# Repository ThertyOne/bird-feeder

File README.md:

# 🐦 Solar Bird Feeder

## 📘 Opis projektu
Projekt to **autonomiczny karmnik dla ptaków z funkcją wykonywania zdjęć**, oparty na module **ESP32-CAM**, zasilany z akumulatora **Li-Po 3,7 V / 2200 mAh**, ładowanego przez ładowarkę **TP4056** z panelem solarnym **6 V / 1 W** (możliwość połączenia 2 paneli szeregowo).  

Z wyjścia baterii energia trafia do **przetwornicy boost 5 V**, zbudowanej od podstaw na bazie generatora **PWM LMC555** i MOSFETa **IRLML6344**, która zasila ESP32 i peryferia – **serwo sterujące karmnikiem, LEDy oświetleniowe oraz czujniki**. Masa wszystkich modułów jest wspólna.  

Ładowanie z panelu odbywa się przez **diodę SS34** i **polyfuse 500 mA**, a napięcie akumulatora jest monitorowane przez dzielnik rezystorowy podłączony do ADC ESP.  

Po wykryciu ruchu przez czujnik ESP wychodzi z trybu **deep sleep**, włącza LED, wykonuje zdjęcie i wysyła je przez Wi-Fi na serwer, po czym ponownie przechodzi w uśpienie, oszczędzając energię. **Peryferia** (serwo, LEDy) są zasilane poprzez **klucz MOSFET**, który odcina zasilanie, gdy peryferia nie działają.

---

## ⚙️ Główne założenia
- Zasilanie autonomiczne: **panel solarny + akumulator Li-Po 3.7 V / 2200 mAh**
- Mikrokontroler i kamera: **ESP32-CAM (OV2640)**
- Komunikacja: **Wi-Fi**, opcjonalnie **LoRaWAN** w przyszłości
- Peryferia:
  - **Ultradźwiękowy czujnik / PIR** – detekcja obecności ptaka
  - **Serwo** – mechanizm podawania karmy
  - **Blue LED matrix 4x4** – doświetlenie sceny podczas zdjęcia
- ESP32 w trybie **deep sleep**, wybudzanie po przerwaniu z czujnika
- Przesyłanie zdjęcia i metadanych (data, godzina) do serwera lub lokalnej bazy danych

---

## ⚡ Przetwornica boost 5 V
- Źródło PWM: **LMC555 @ ~100 kHz, 3.3 V**
- MOSFET: **IRLML2502 / IRLML6344**
- Cewka: **15 μH**
- Dioda: **SS34**
- Kondensator wyjściowy: **4700 μF**
- Ograniczenie napięcia: **Zener 5 V**
- Funkcja: podnosi napięcie z 3,7 V akumulatora Li-Po do stabilnych 5 V dla ESP32 i peryferiów

---

## 🔋 Szacowane zużycie prądu
| Moduł            | Tryb/obciążenie             | Prąd (mA) |
|-----------------|----------------------------|------------|
| ESP32-CAM       | Deep sleep                 | 0.1 – 0.2 |
| ESP32-CAM       | Aktywne (Wi-Fi + foto)     | 180 – 250 |
| Serwo           | Ruch                        | 150 – 200 |
| LEDy            | Max 4 LED                   | 80 – 100 |
| Czujniki        | Idle                        | 2 – 5      |

**Średni pobór prądu:** ~10–30 mA przy większości czasu w deep sleep.  
**Maksymalny chwilowy pobór:** ~500 mA przy jednoczesnym ruchu serwa i LED.

---

## 💡 Sposoby oszczędzania energii
- ESP32 w **deep sleep**, wybudzenie tylko przy wykryciu ruchu
- Peryferia (LED, serwo) zasilane przez **MOSFET**, odcięcie zasilania gdy nieaktywne
- Minimalizacja czasu pracy Wi-Fi i kamer
- Możliwość zmniejszenia jasności LED i liczby LED w pierścieniu
- Optymalizacja częstotliwości wybudzeń w zależności od natężenia odwiedzin ptaków

---

## ☀️ Energia z baterii i paneli
- **Akumulator Li-Po:** 3,7 V / 2200 mAh → **8,14 Wh**
- **Panel solarny:** 6 V / 1 W → maksymalny prąd ładowania ~167 mA (przy pełnym słońcu)
- **2 panele szeregowo:** napięcie 12 V / prąd ~83 mA, dalej prostownik i TP4056
- **Przetwornica boost 5 V:** sprawność ~85 % → prąd pobierany z akumulatora = Iout × 5 V / (η × 3,7 V)
- **Szacowany średni pobór prądu ESP32 + peryferia:** 50 mA @ 5 V  
  I_bat ≈ (5V * 0.05A) / (0.85 * 3.7V) ≈ 79,5 mA
- **Czas pracy na baterii bez słońca:**  
  Czas pracy na baterii ≈ 2200 mAh / 79,5 mA ≈ 27,7 h ≈ 1,15 dnia
- **Chwilowe piki prądu** (serwo + LED + Wi-Fi): ~500 mA @ 5 V → Ibat_peak ≈ 800 mA  
- **Przy słonecznej pogodzie** panele mogą praktycznie utrzymać akumulator w pełnym stanie, a nawet doładować go na zapas (np. 4–5 h słońca → ~4 Wh energii)

---

## 🔧 Uwagi do przetwornicy
- Układ **boost 5 V** przy chwilowych pikach prądu (serwo + LED + Wi-Fi) mogą wystąpić spadki napięcia
- Kondensator 4700 μF pomaga w wygładzaniu napięcia przy skokach prądowych
- Zener 5 V chroni ESP32 przed przepięciem, ale warto monitorować temperaturę MOSFETa i cewki przy pełnym obciążeniu
- Ewentualne zwiększenie cewki lub dodanie małego kondensatora ceramicznego przy MOSFET zwiększy stabilność przy dużym poborze

---

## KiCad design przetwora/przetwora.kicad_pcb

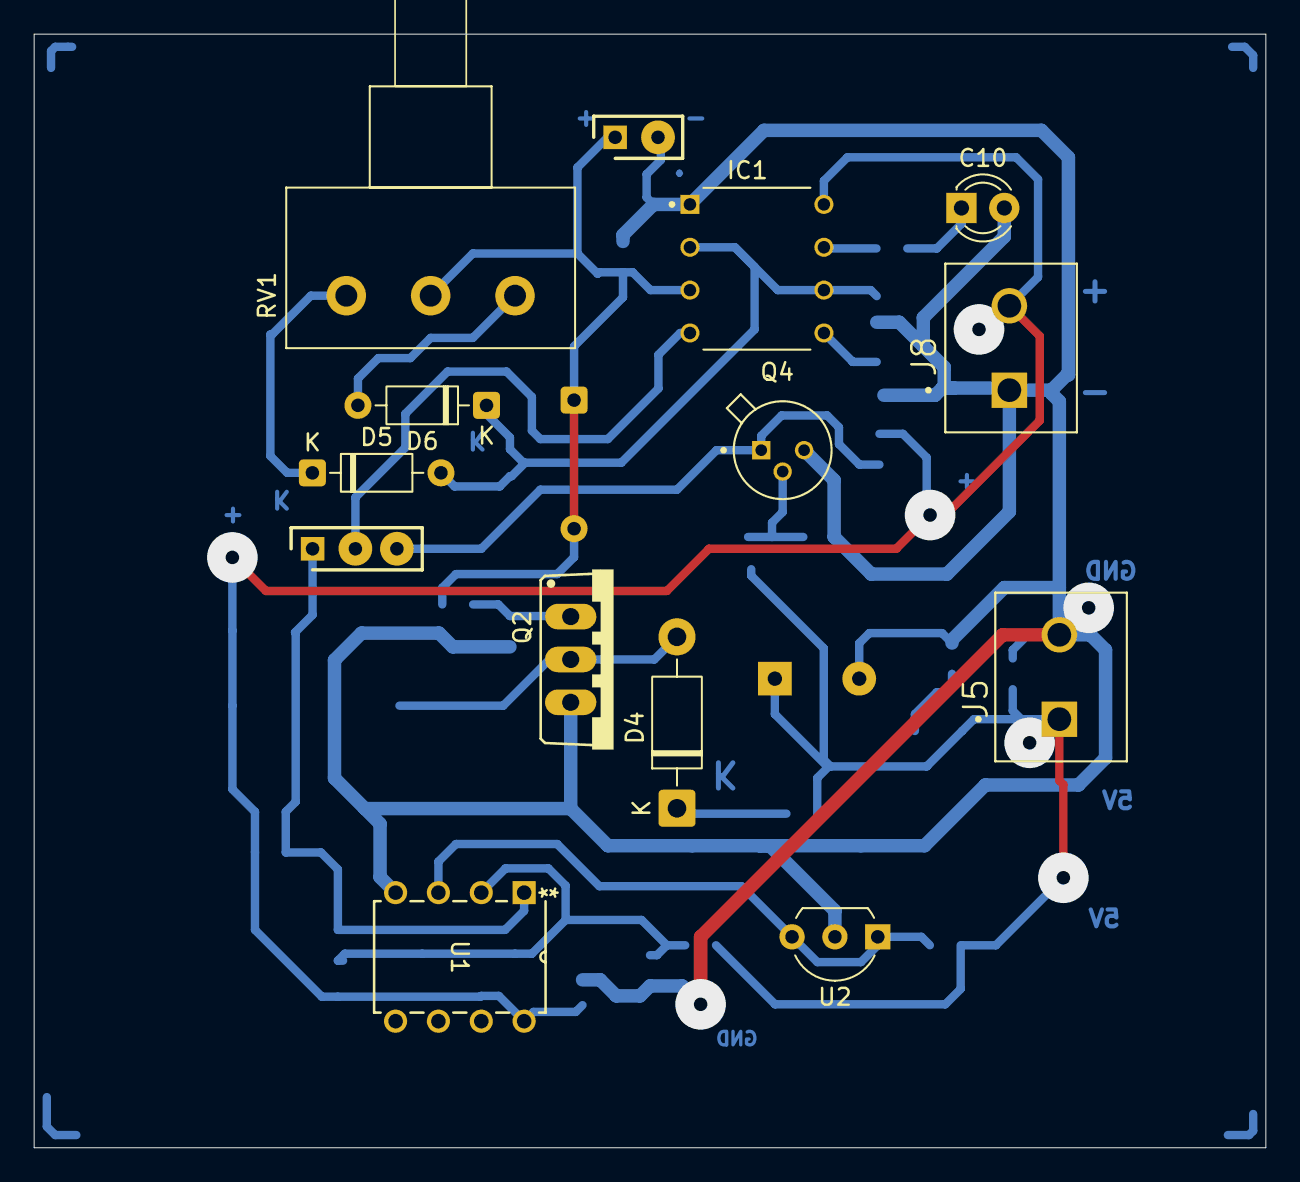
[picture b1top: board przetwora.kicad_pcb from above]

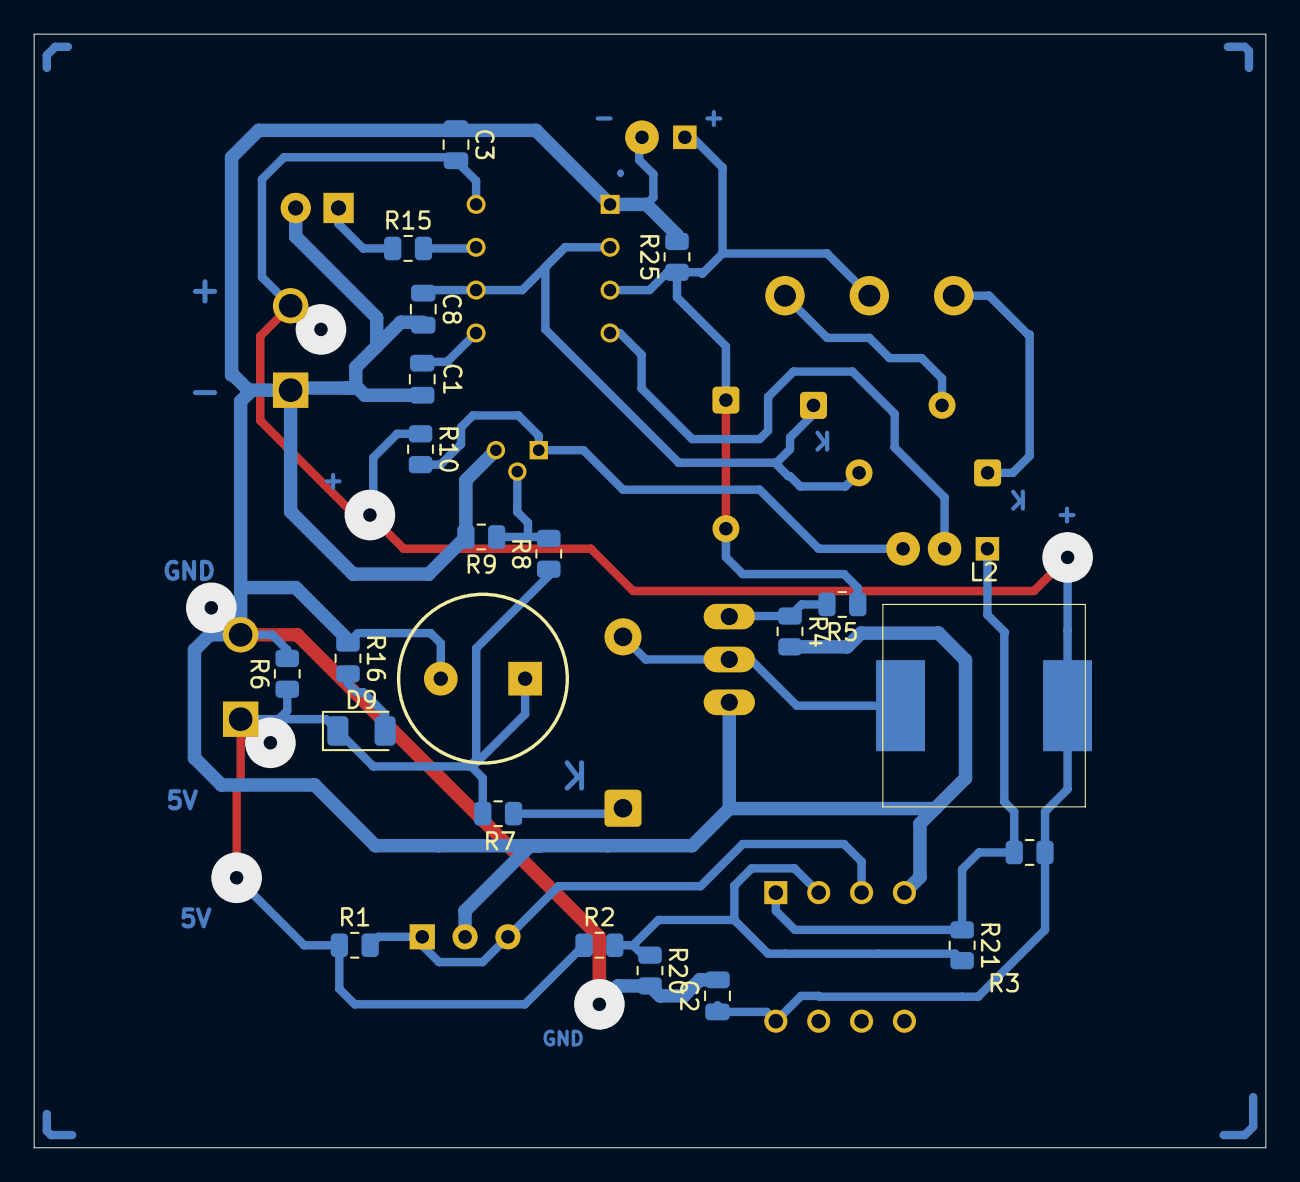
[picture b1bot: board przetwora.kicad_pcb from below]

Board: 2 copper layers, 73.0 x 66.0 mm, 37 parts (22 on the bottom side), 18 nets.

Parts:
C1, C8: 10n; C_0805_2012Metric
C2, C3: 100n; C_0805_2012Metric
C8#2: 4700 μ; electrolytic_CAPPRD500W65D1000H2700
C10: 100n; LED_D3.0mm
D4: 1N5818; D_DO-41_SOD81_P10.16mm_Horizontal
D5, D5#2, D6: 1N4148; D_DO-35_SOD27_P7.62mm_Horizontal
D9: 5.1 V; D_1206_3216Metric
IC1: lmc555; LMC555
J5: 5V_step_up; roaster_3_5
J6, J6#2: cont_3_5; pin_2_RHDR4W60P0X254_1X4_1016X250X840P_1
J8: baterry; roaster_3_5
L2: ETQP4M150KFN; cewka_DE1207
Q2: IRF740; irf740_TO220BV
Q4: NPN; 2N2222_TO127P580H530-3
R1: 680; R_0805_2012Metric
R2, R3, R4, R15, R20, R25: 10k; R_0805_2012Metric
R5, R10: 100; R_0805_2012Metric
R6: load test; R_0805_2012Metric
R7: 6.8; R_0805_2012Metric
R8: 4.7k; R_0805_2012Metric
R9: 1k; R_0805_2012Metric
R16: 470; R_0805_2012Metric
R21: 470k; R_0805_2012Metric
RV1: 10k; Potentiometer_Omeg_PC16BU_Horizontal
U1: LM393P; LM393
U2: TL431D; TO-92L_Inline_Wide

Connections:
+2V5: R1.2, U1.3 (1IN+), U2.1 (K), U2.3 (REF)
BAT: C2.1, C3.2, IC1.8 (V+), J8.2, L2.2, R3.1, R10.1, U1.8 (VCC)
GND: C1.2, C2.2, C3.1, C8.2, C10.2 (A), IC1.1 (GND), J5.2, J8.1, Q2.S, Q4.3 (E), R4.2, R6.2, R9.2, R16.1, R20.2, R25.2, U1.4 (GND), U2.2 (A)
unnamed: D4.1 (K), R7.1
unnamed: C10.1 (K), R15.1
unnamed: D4.2 (A), L2.1, Q2.D
unnamed: D5.1 (K), RV1.3
unnamed: D6.2 (A), RV1.1
unnamed: D9.2 (A), R16.2
unnamed: C1.1, IC1.5 (CV)
unnamed: IC1.7 (DIS), R15.2
unnamed: Q2.G, R4.1, R5.2
unnamed: Q4.2 (B), R8.2, R9.1
unnamed: R2.2, R20.1, R21.2, U1.2 (1IN-)
PWM_out: D5#2.1 (K), D5#2.2 (A), IC1.3 (OUT), R5.1, R25.1, RV1.2
reset: IC1.4 (~RST), J6.1, J6.2, J6.3 (2), Q4.1 (C), R3.2, R10.2, R21.1, U1.1 (1OUT)
step_up: D9.1 (K), J5.1, R1.1, R2.1, R6.1, R7.2, R8.1
trig: C8.1, D5.2 (A), D6.1 (K), IC1.2 (~TRIG), IC1.6 (THRS)

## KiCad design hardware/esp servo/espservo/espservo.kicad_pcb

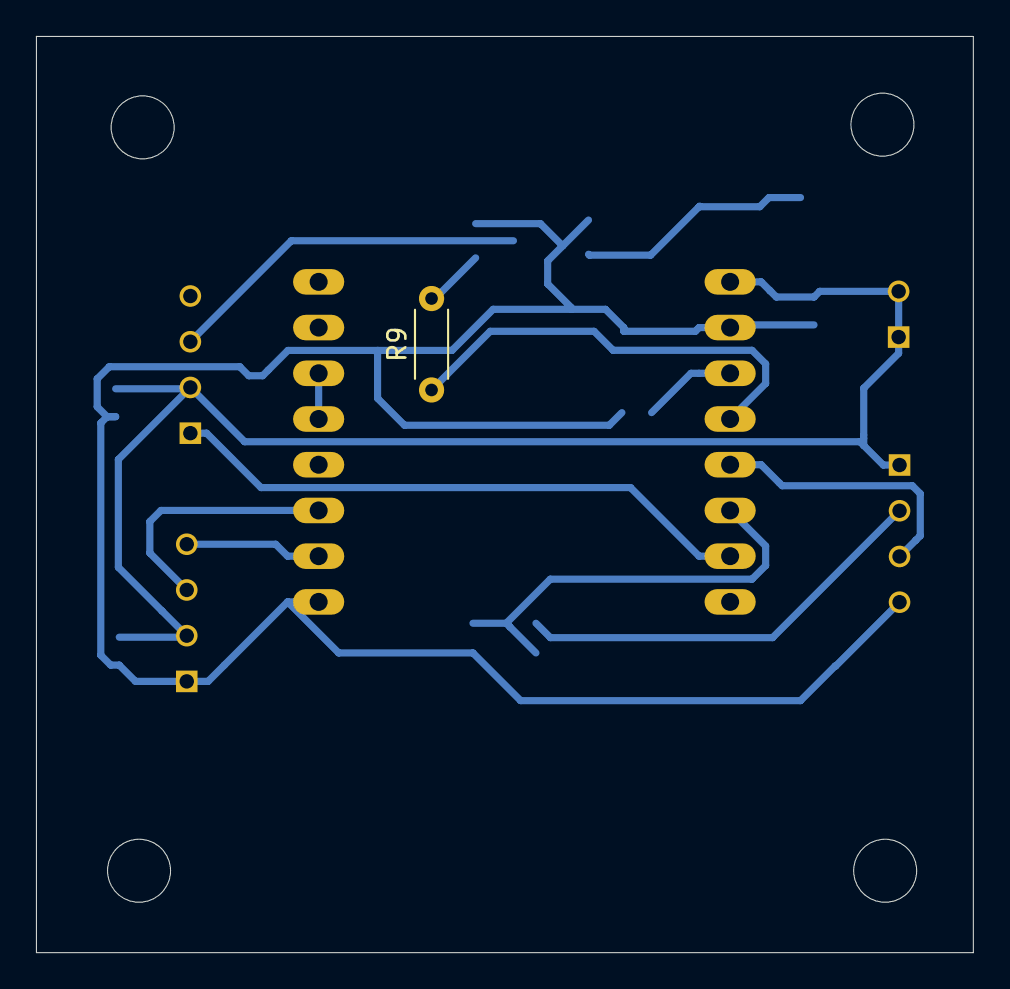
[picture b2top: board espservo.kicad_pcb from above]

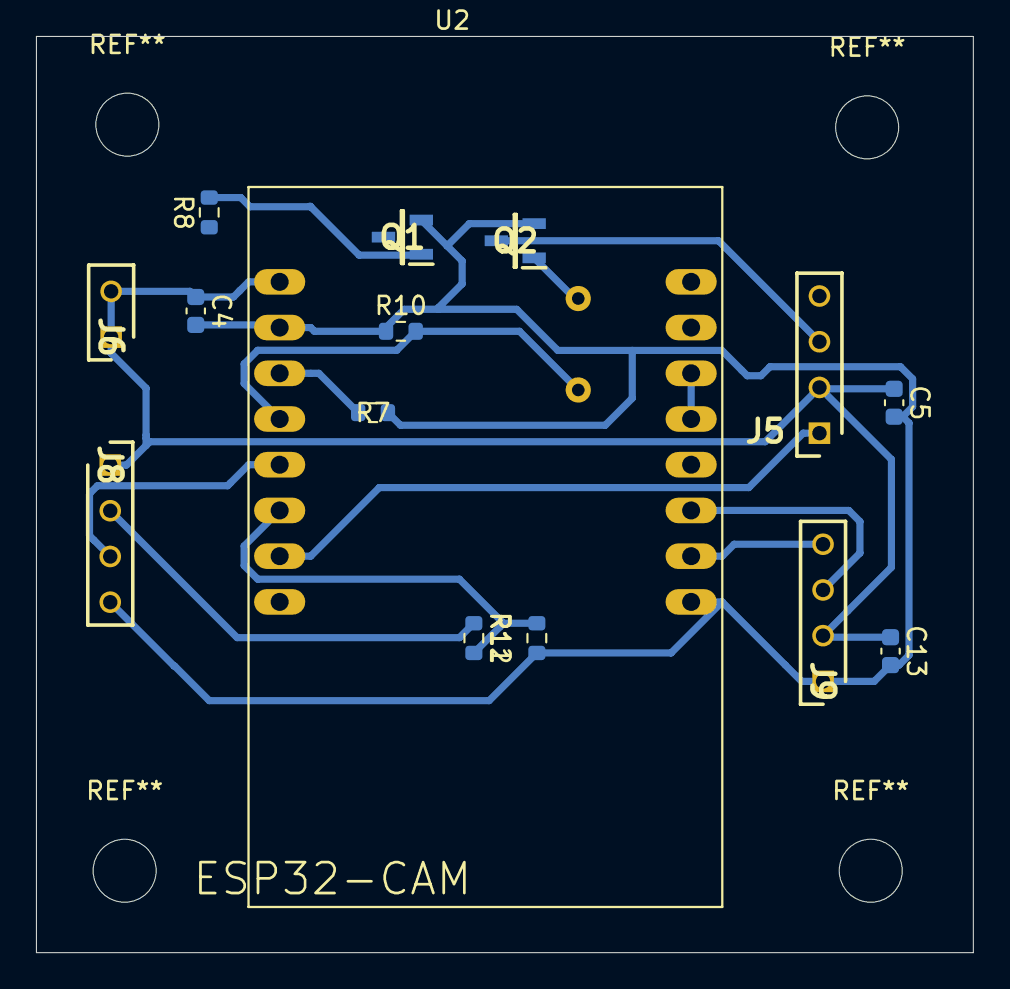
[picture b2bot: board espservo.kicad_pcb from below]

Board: 2 copper layers, 52.0 x 50.9 mm, 16 parts (15 on the bottom side), 14 nets.

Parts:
C4: 10 μ; C_0603_1608Metric
C5: 100 μ; C_0603_1608Metric
C13: 1 μ; C_0603_1608Metric
J5: servo; pin_4_RHDR4W60P0X254_1X4_1016X250X840P
J6: 5V_DC/DC; pin_2_RHDR4W60P0X254_1X4_1016X250X840P_1
J8: ultrasonic; pin_4_RHDR4W60P0X254_1X4_1016X250X840P
J9: UART; pin_4_RHDR4W60P0X254_1X4_1016X250X840P
Q1, Q2: IRLML2502TRPBF; IRL_SOT95P237X112-3N
R7, R10: 100 k; R_0603_1608Metric
R8: 100; R_0603_1608Metric
R9: 100; R_Axial_DIN0204_L3.6mm_D1.6mm_P5.08mm_Horizontal
R11: 10 k; R_0603_1608Metric
R12: 20 k; R_0603_1608Metric
U2: ESP32-CAM

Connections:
+5V: C4.1, C5.1, C13.1, J5.2, J6.1, J6.2, J8.1, J9.2, U2.P$1 (5V)
GND: C4.2, C5.2, C13.2, J8.4, J9.1, Q1.2 (S), Q2.2 (S), R7.1, R10.1, R12.2, U2.P$2 (GND), U2.P$9 (.GND)
unnamed: Q1.1 (G), R8.2
unnamed: Q2.1 (G), R9.2
unnamed: U2.P$13 (GND.), U2.P$14 (IO0)
unnamed: R7.2, R8.1, U2.P$3 (IO12)
unnamed: R9.1, R10.2, U2.P$4 (IO13)
unnamed: R11.2, R12.1, U2.P$6 (IO14)
UOR: J9.3, U2.P$11 (IO3/U0R)
UOT: J9.4, U2.P$10 (IO1/U0T)
echo: J8.2, R11.1
servo_GND: J5.3, Q2.3 (D)
servo_PWM: J5.1, U2.P$7 (IO2)
trig: J8.3, U2.P$5 (IO15)

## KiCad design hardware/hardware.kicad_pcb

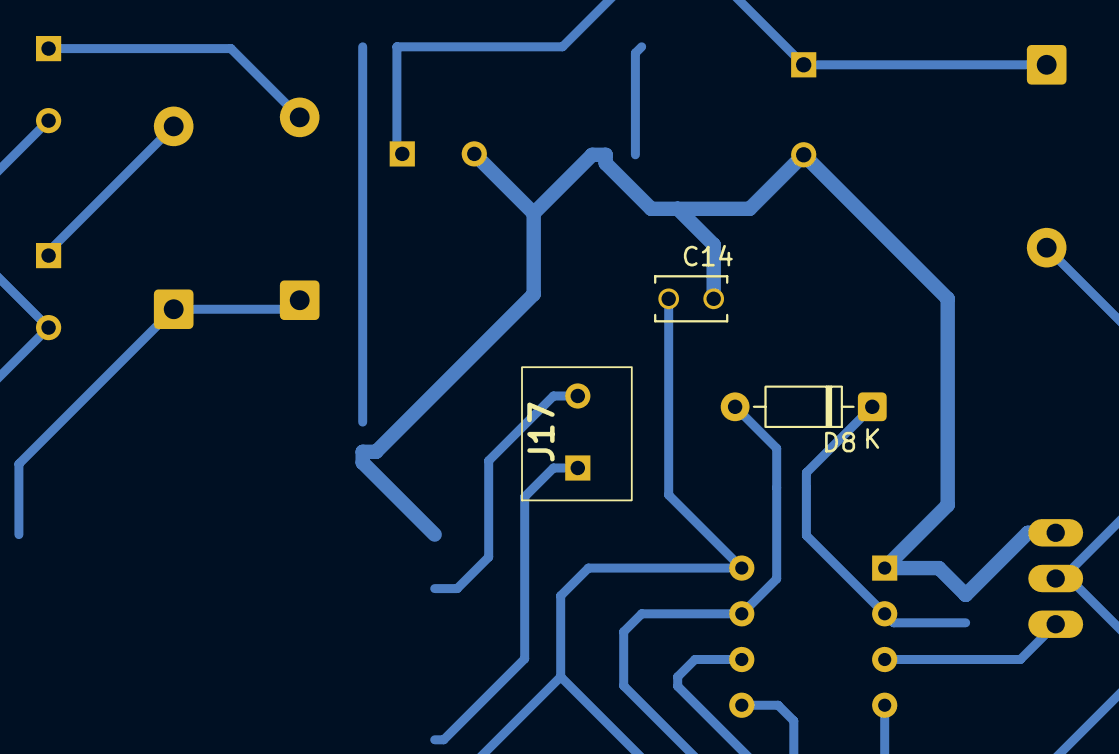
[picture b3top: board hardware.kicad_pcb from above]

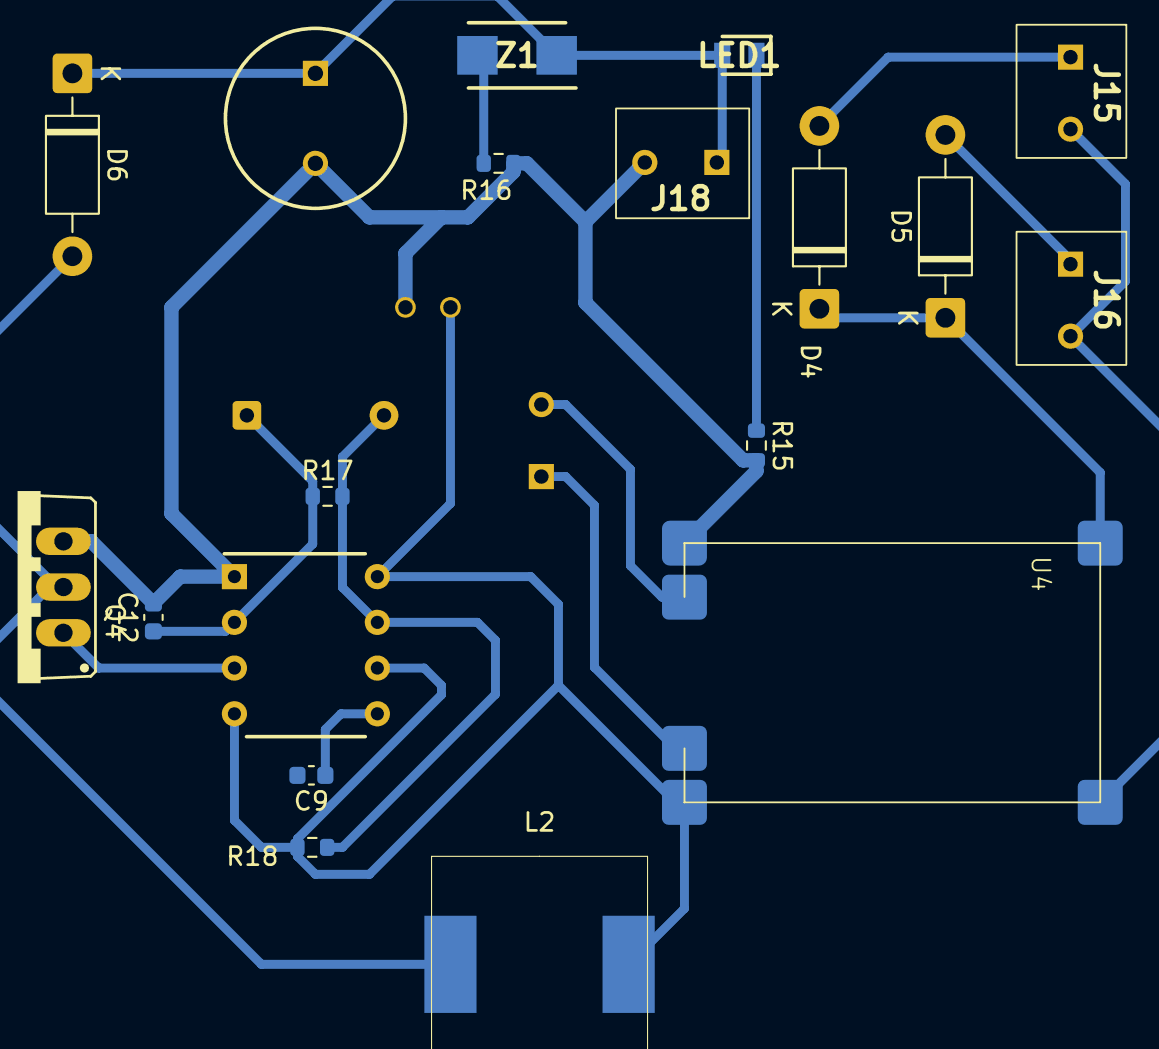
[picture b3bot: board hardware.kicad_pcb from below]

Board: 2 copper layers, 22 parts (19 on the bottom side), 16 nets.

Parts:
C8: 4700 μ; electrolytic_CAPPRD500W65D1000H2700
C9, C12: 1 n; C_0603_1608Metric
C14: 10 μ; CAPRB250W50L400T250H550
D4, D5: SS34; D_DO-41_SOD81_P10.16mm_Horizontal
D6: 1N5818; D_DO-41_SOD81_P10.16mm_Horizontal
D8: 1N4148; D_DO-35_SOD27_P7.62mm_Horizontal
IC1: NE555; LMC555_DIP794W53P254L959H508Q8N
J15, J16: Solar panel; ARK raster 2,54 mm
J17: Li-Po battery; ARK raster 2,54 mm
J18: Screw_Terminal_01x02; ARK raster 2,54 mm
L2: ETQP4M150KFN; DE1207
LED1: 5 V; LEDC2012X40N
Q4: IRF740
R15, R16: 470; R_0603_1608Metric
R17: 15 k; R_0603_1608Metric
R18: 1 k; R_0603_1608Metric
U4: TP4056
Z1: 1SMB5918BT3G; zenner_DIOM5436X247N

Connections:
+5V: C8.1 (+), D6.1 (K), J18.1, LED1.2 (A), Z1.1 (K)
BAT: C14.1, IC1.4 (~RESET), IC1.8 (V+), L2.2, R18.2, U4.3 (OUT_+)
GND: C8.2 (-), C9.2, C12.2, C14.2, IC1.1 (GROUND), J18.2, Q4.S, R15.2, R16.2, U4.6 (OUT_-)
unnamed: D4.2 (A), J15.1
unnamed: D4.1 (K), D5.1 (K), U4.1 (+)
unnamed: D5.2 (A), J16.1
unnamed: D6.2 (A), L2.1, Q4.D
unnamed: D8.2 (A), IC1.7 (DISCHARGE), R17.2, R18.1
unnamed: C12.1, D8.1 (K), IC1.2 (~TRIGGER), R17.1
unnamed: C9.1, IC1.5 (CONTROL_VOLTAGE)
unnamed: J15.2, J16.2, U4.2 (-)
unnamed: J17.1, U4.4 (B_+)
unnamed: J17.2, U4.5 (B_-)
unnamed: LED1.1 (K), R15.1
unnamed: R16.1, Z1.2 (A)
PWM: IC1.3 (OUTPUT), Q4.G

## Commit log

2025-10-17 praca na piatek
2025-10-19 mam dosc
2025-10-19 aleluja i do poniedzialku
2025-10-21 jazda z dc/dc
2025-10-24 przetwornica my ass
2025-10-26 Aktualny stan projektu
2025-10-26 milo tak zrobic sym
2025-10-26 poprawa readme
2025-10-27 aleluja
2025-10-27 dobranoc
2025-10-28 open lab
2025-10-28 karygodna nieobecnosc Wojtusiow
2025-10-29 lecisz z tym Janek
2025-12-13 za Janka
2026-01-04 nowa wersja
2026-03-12 Preparing Src directory for codebase
2026-05-12 Update gitignore
2026-05-12 Add code readme
2026-05-12 first functionality
2026-05-12 Add platform.ini
2026-05-13 Add camera functionality
2026-05-18 Setup and tests finnished. Main loop to go.
2026-05-19 Restoring config after an accident
2026-05-19 Figured PIR sensor. Added automatic mode
2026-05-19 raport and presentation
2026-05-27 Integrated a new sensor
2026-05-27 Upgreaded timing control for better performance
2026-05-27 small rearragmment of raport files
